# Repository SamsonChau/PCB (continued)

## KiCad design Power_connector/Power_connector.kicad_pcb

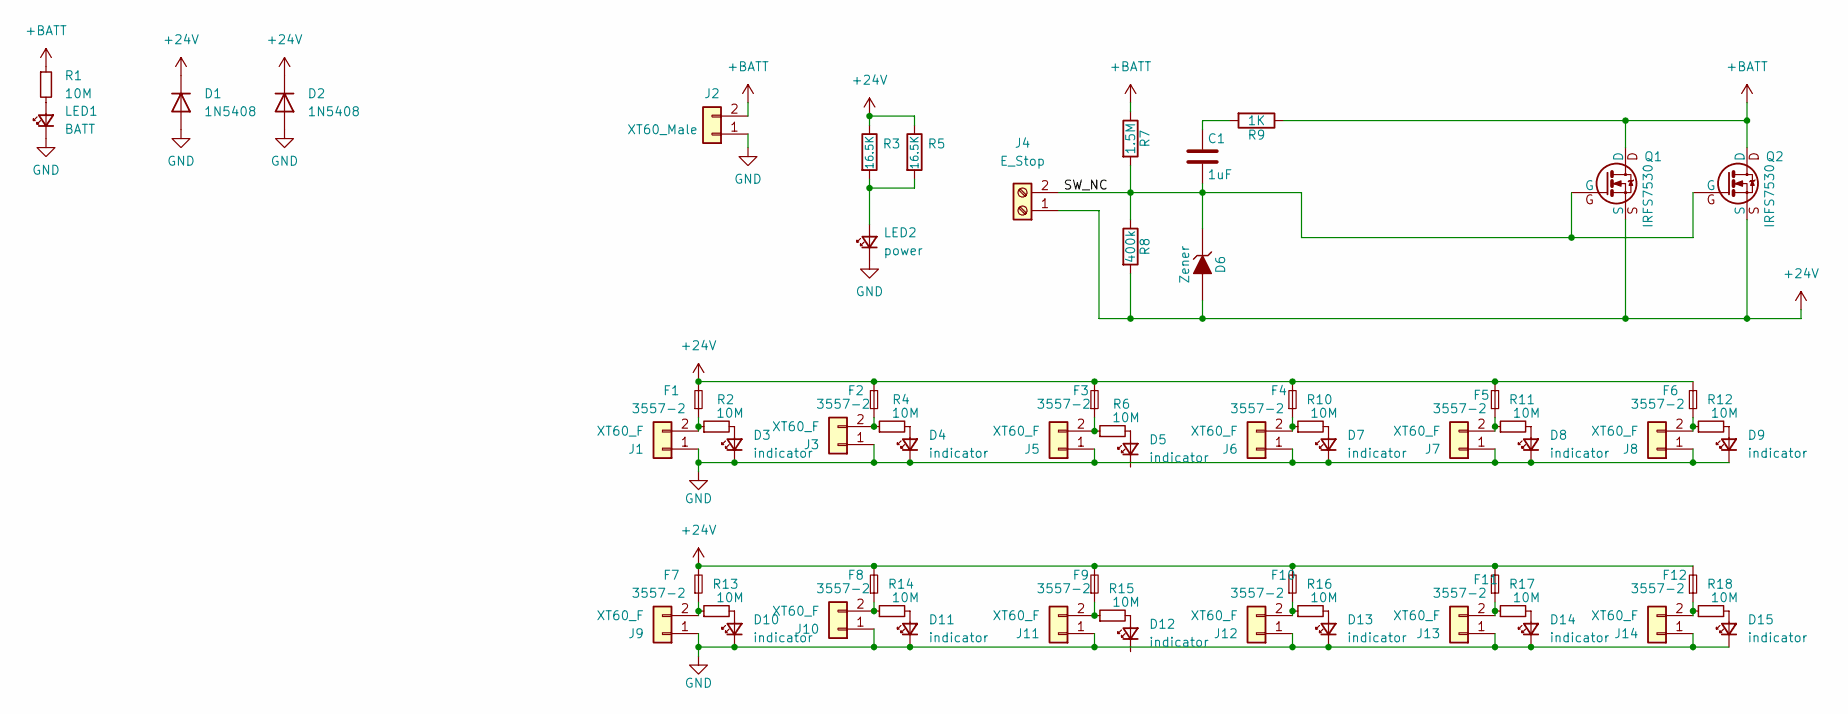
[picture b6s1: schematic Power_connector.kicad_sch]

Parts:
C1: 1uF; C_0805_2012Metric_Pad1.18x1.45mm_HandSolder
D1, D2: 1N5408; D_DO-201AD_P15.24mm_Horizontal
D3, D4, D5, D7, D8, D9, D10, D11, D12, D13, D14, D15: indicator; LED_0805_2012Metric
D6: Zener; D_SOD-123F
F1, F2, F3, F4, F5, F6, F7, F8, F9, F10, F11, F12: 3557-2; FUSE_3557-2
J1, J3, J5, J6, J7, J8, J9, J10, J11, J12, J13, J14: XT60_F; AMASS_XT60-F_1x02_P7.20mm_Vertical
J2: XT60_Male
J4: E_Stop; TerminalBlock_Phoenix_MKDS-1,5-2-5.08_1x02_P5.08mm_Horizont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
LED1: BATT; LED_0805_2012Metric_Pad1.15x1.40mm_HandSolder
LED2: power; LED_0805_2012Metric_Pad1.15x1.40mm_HandSolder
Q1, Q2: IRFS7530; D2PAK-7-GDS
R1, R2, R4, R6, R10, R11, R12, R13, R14, R15, R16, R17, R18: 10M; R_0805_2012Metric
R3, R5: 16.5K; R_1206_3216Metric_Pad1.30x1.75mm_HandSolder
R7: 1.5M; R_0805_2012Metric_Pad1.20x1.40mm_HandSolder
R8: 400k; R_0805_2012Metric_Pad1.20x1.40mm_HandSolder
R9: 1K; R_0805_2012Metric_Pad1.20x1.40mm_HandSolder

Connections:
+24V: D1.1 (K), D2.1 (K), D6.2 (A), F1.2, F2.2, F3.2, F4.2, F5.2, F6.2, F7.2, F8.2, F9.2, F10.2, F11.2, F12.2, J4.1, Q1.S, Q2.S, R3.1, R5.1, R8.2
+BATT: J2.2, Q1.D, Q2.D, R1.1, R7.1, R9.1
/SW_NC: C1.2, D6.1 (K), J4.2, Q1.G, Q2.G, R7.2, R8.1
GND: D1.2 (A), D2.2 (A), D3.1 (K), D4.1 (K), D7.1 (K), D8.1 (K), D9.1 (K), D10.1 (K), D11.1 (K), D13.1 (K), D14.1 (K), D15.1 (K), J1.1, J2.1, J3.1, J5.1, J6.1, J7.1, J8.1, J9.1, J10.1, J11.1, J12.1, J13.1, J14.1, LED1.1 (K), LED2.1 (K)
unnamed: C1.1, R9.2
unnamed: D3.2 (A), R2.2
unnamed: D4.2 (A), R4.2
unnamed: D5.2 (A), R6.2
unnamed: D7.2 (A), R10.2
unnamed: D8.2 (A), R11.2
unnamed: D9.2 (A), R12.2
unnamed: D10.2 (A), R13.2
unnamed: D11.2 (A), R14.2
unnamed: D12.2 (A), R15.2
unnamed: D13.2 (A), R16.2
unnamed: D14.2 (A), R17.2
unnamed: D15.2 (A), R18.2
unnamed: F1.1, J1.2, R2.1
unnamed: F2.1, J3.2, R4.1
unnamed: F3.1, J5.2, R6.1
unnamed: F4.1, J6.2, R10.1
unnamed: F5.1, J7.2, R11.1
unnamed: F6.1, J8.2, R12.1
unnamed: F7.1, J9.2, R13.1
unnamed: F8.1, J10.2, R14.1
unnamed: F9.1, J11.2, R15.1
unnamed: F10.1, J12.2, R16.1
unnamed: F11.1, J13.2, R17.1
unnamed: F12.1, J14.2, R18.1
unnamed: LED1.2 (A), R1.2
unnamed: LED2.2 (A), R3.2, R5.2

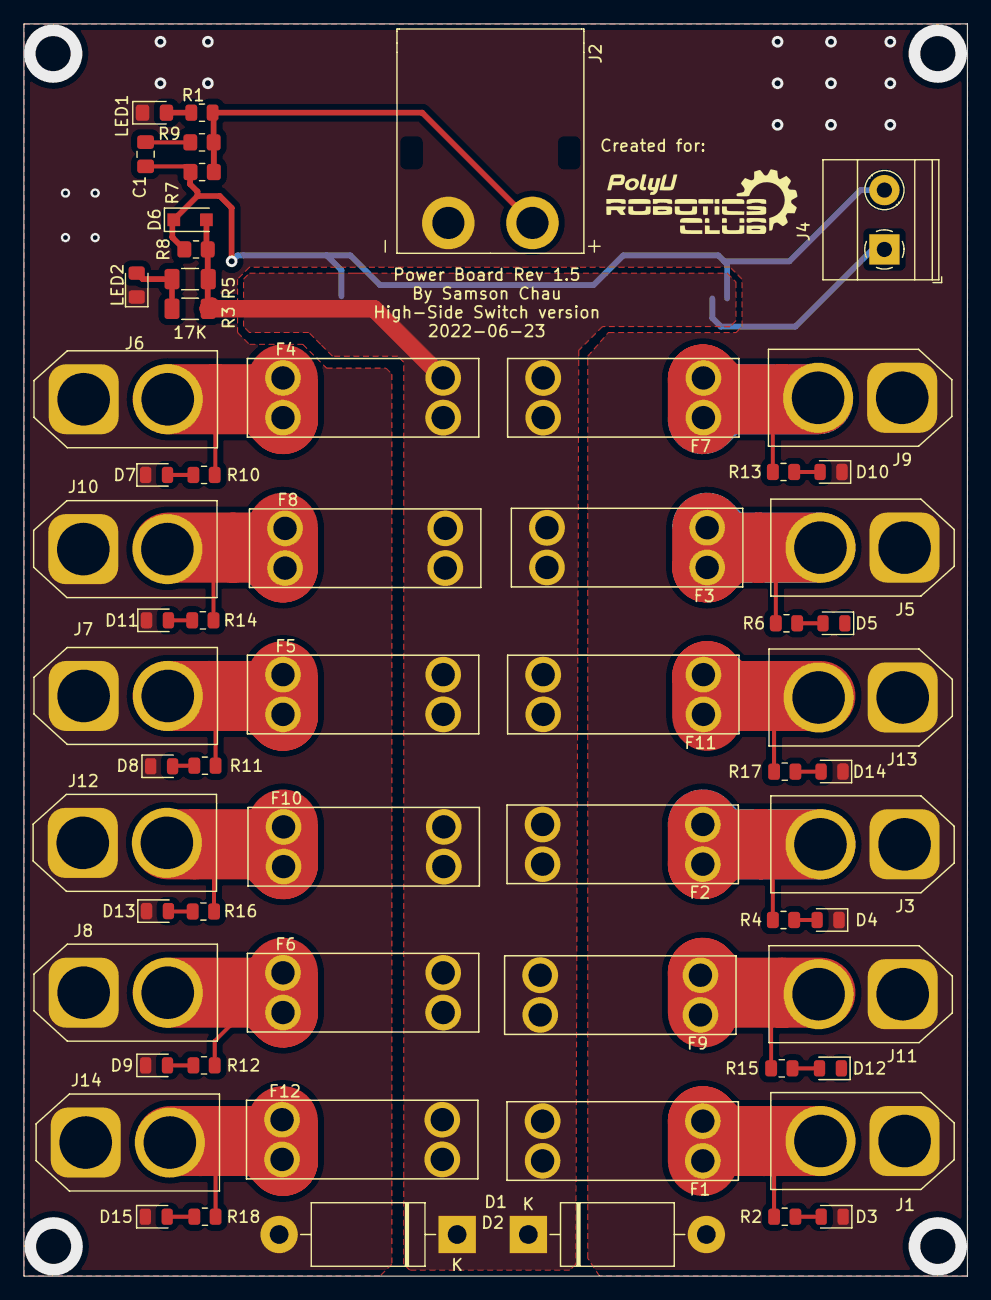
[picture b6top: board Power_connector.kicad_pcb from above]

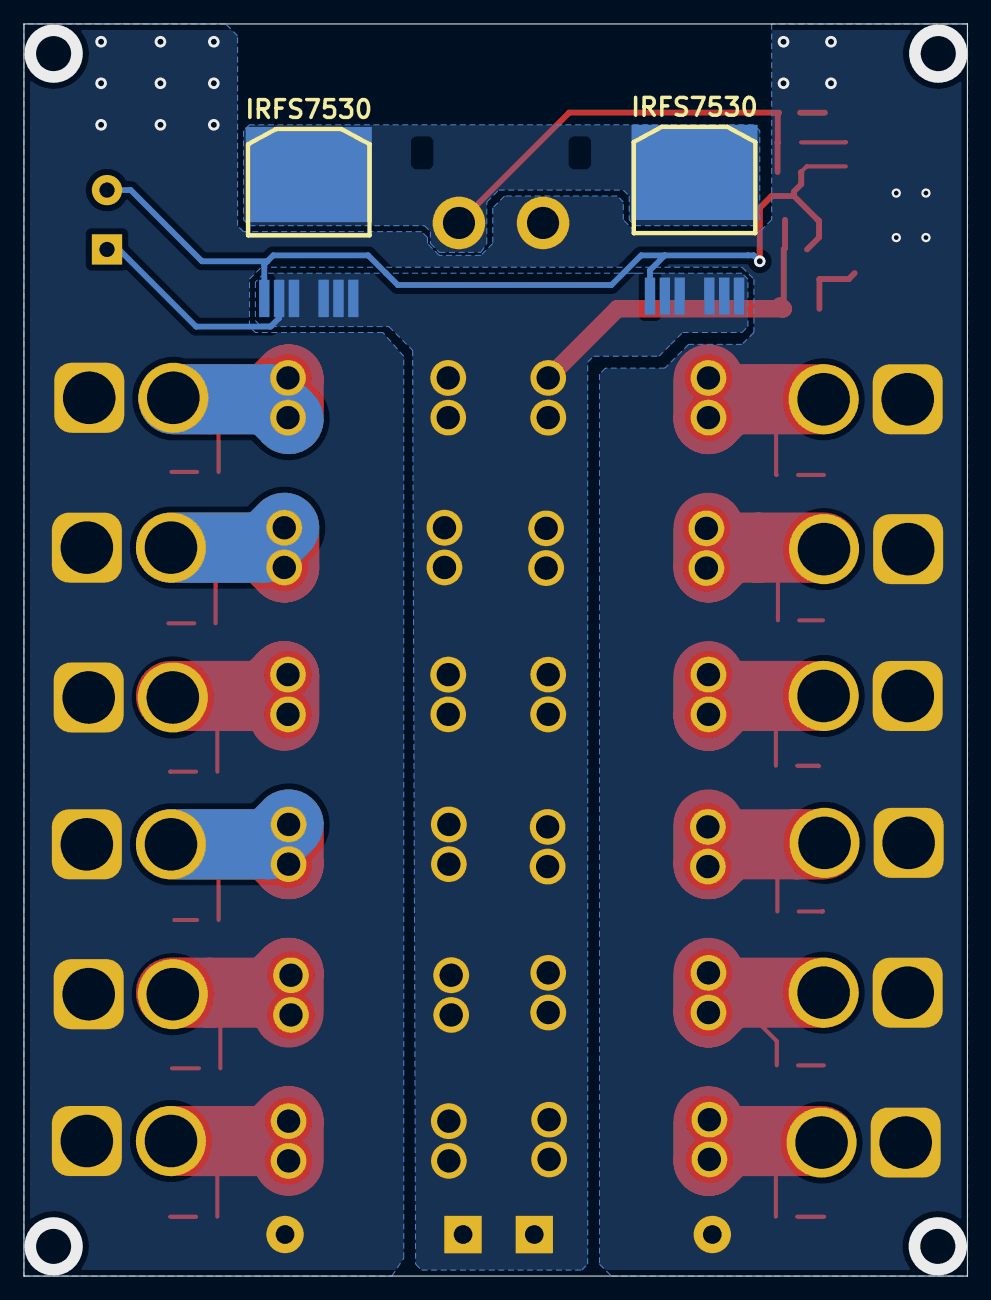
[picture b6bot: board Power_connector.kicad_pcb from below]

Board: 2 copper layers, 80.8 x 107.2 mm, 64 parts (2 on the bottom side), 31 nets.

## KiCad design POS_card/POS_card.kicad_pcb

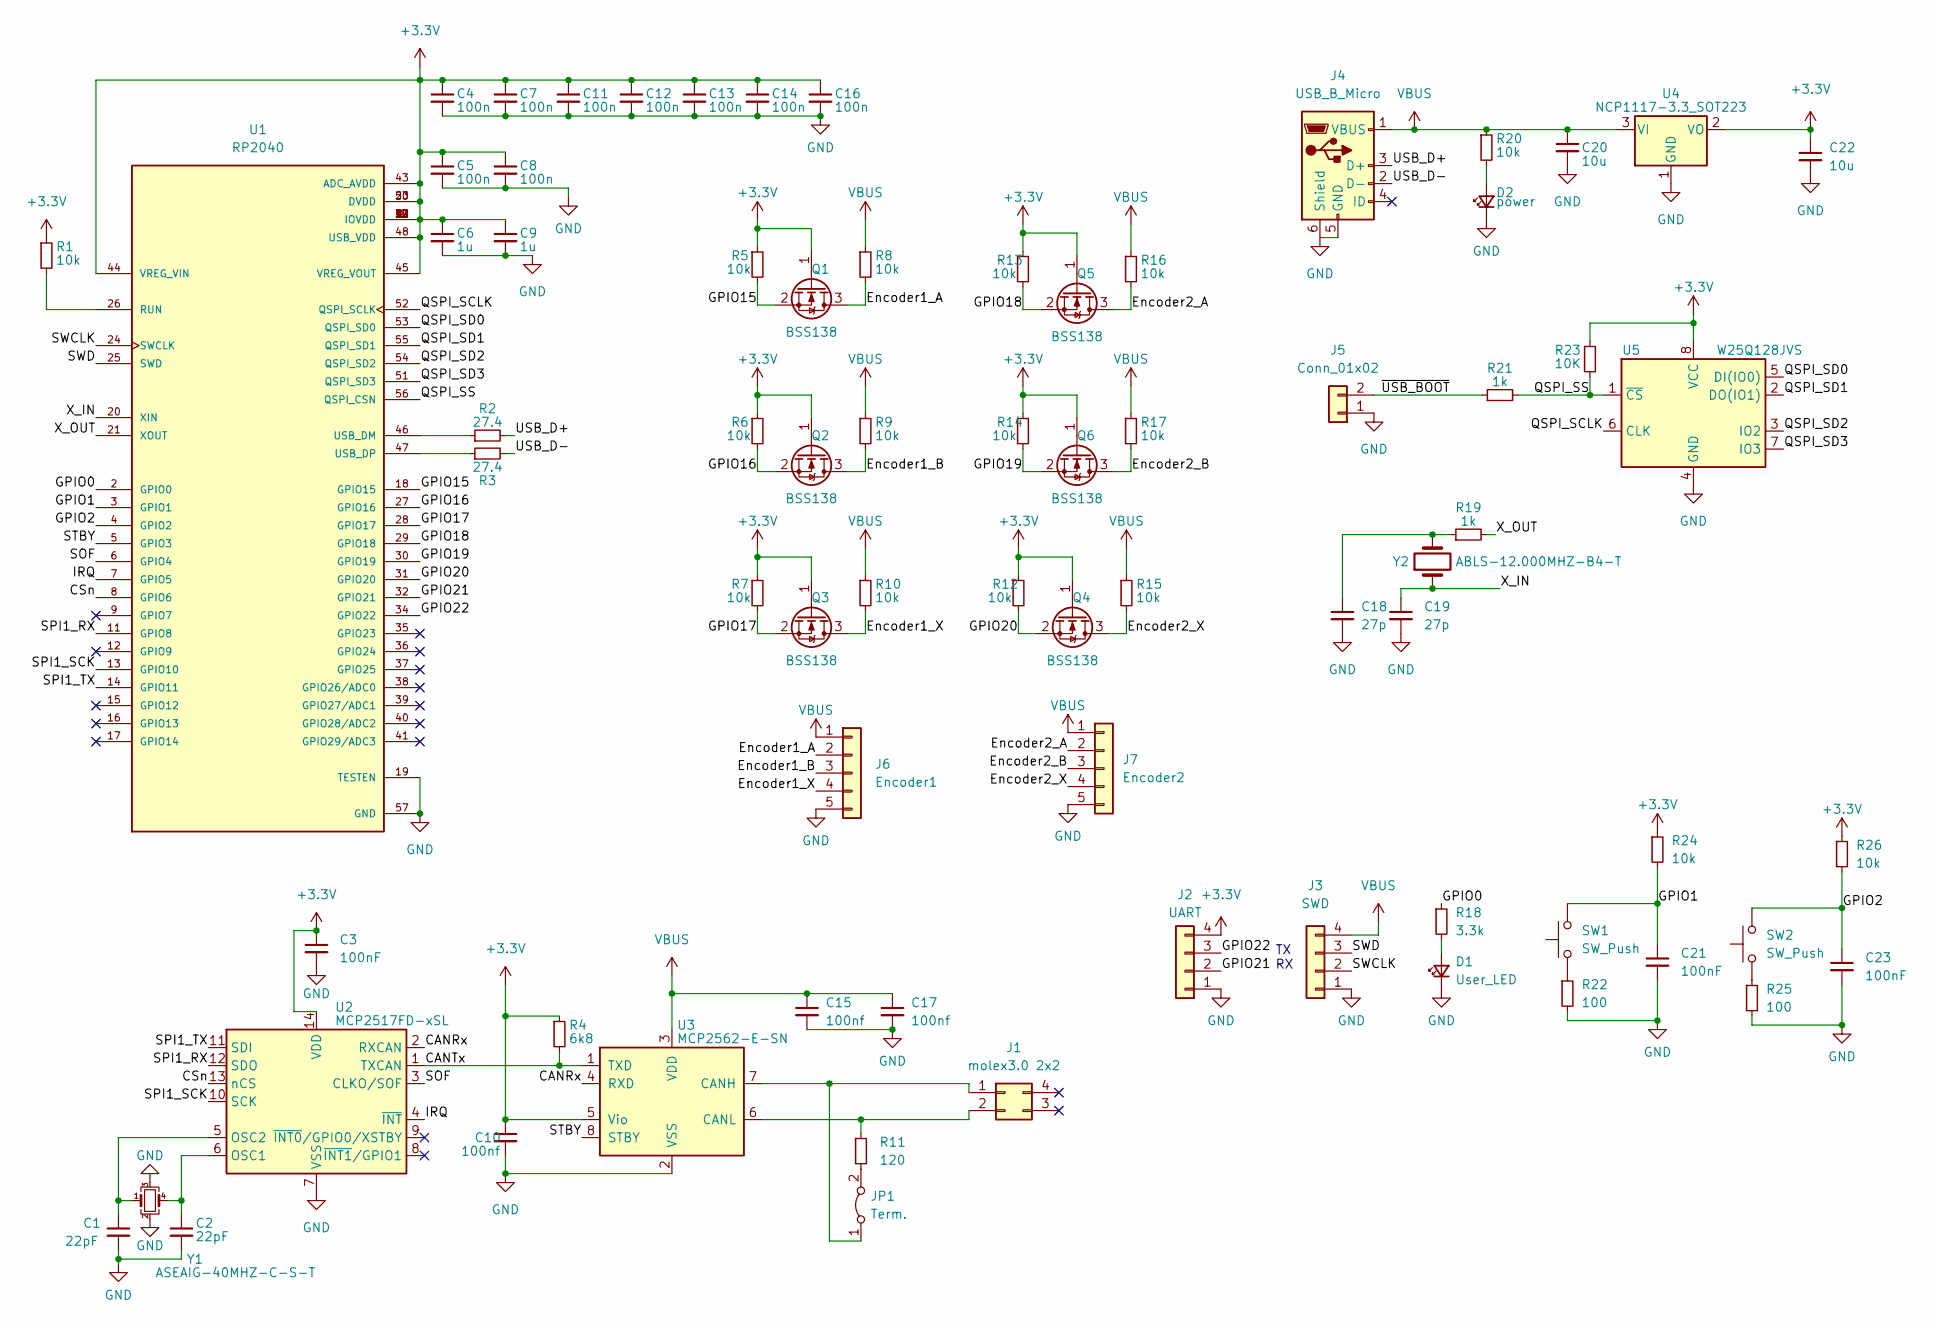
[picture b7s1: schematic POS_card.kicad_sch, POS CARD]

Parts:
C1, C2: 22pF; C_0402_1005Metric
C3, C21: 100nF; C_0402_1005Metric
C4, C5, C7, C8, C11, C12, C13, C14, C16: 100n; C_0402_1005Metric
C6, C9: 1u; C_0402_1005Metric
C10, C15, C17: 100nf; C_0402_1005Metric
C18, C19: 27p; C_0402_1005Metric
C20, C22: 10u; C_0603_1608Metric
C23: 100nF; C_0402_1005Metric_Pad0.74x0.62mm_HandSolder
D1: User_LED; LED_0402_1005Metric
D2: power; LED_0402_1005Metric
J1: molex3.0 2x2; Molex_Micro-Fit_3.0_43045-0412_2x02_P3.00mm_Vertical
J2: UART; PinHeader_1x04_P2.54mm_Vertical
J3: SWD; PinHeader_1x04_P2.54mm_Vertical
J4: USB_B_Micro; USB_Micro-B_Molex-105017-0001
J5: Conn_01x02; PinHeader_1x02_P2.54mm_Vertical
J6: Encoder1; JST_PH_B5B-PH-K_1x05_P2.00mm_Vertical
J7: Encoder2; JST_PH_B5B-PH-K_1x05_P2.00mm_Vertical
JP1: Term.; TestPoint_Bridge_Pitch2.0mm_Drill0.7mm
Q1, Q2, Q3, Q4, Q5, Q6: BSS138; SOT-23
R1, R5, R6, R7, R8, R9, R10, R12, R13, R14, R15, R16, R17, R20, R24, R26: 10k; R_0402_1005Metric
R2, R3: 27.4; R_0402_1005Metric
R4: 6k8; R_0402_1005Metric
R11: 120; R_0402_1005Metric
R18: 3.3k; R_0402_1005Metric
R19, R21: 1k; R_0402_1005Metric
R22, R25: 100; R_0402_1005Metric
R23: 10K; R_0402_1005Metric
SW1, SW2: SW_Push; SW_Push_1P1T_NO_6x6mm_H9.5mm
U1: RP2040; QFN40P700X700X90-57N; PARTREV 1.6.1
U2: MCP2517FD-xSL; SOIC-14_3.9x8.7mm_P1.27mm
U3: MCP2562-E-SN; SOIC-8_3.9x4.9mm_P1.27mm
U4: NCP1117-3.3_SOT223; SOT-223-3_TabPin2
U5: W25Q128JVS; SOIC-8_5.23x5.23mm_P1.27mm
Y1: ASEAIG-40MHZ-C-S-T; Crystal_SMD_TXC_7M-4Pin_3.2x2.5mm
Y2: ABLS-12.000MHZ-B4-T; Crystal_SMD_HC49-SD

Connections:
+3V3: C3.1, C4.1, C5.1, C6.1, C7.1, C8.1, C9.1, C10.1, C11.1, C12.1, C13.1, C14.1, C16.1, C22.1, J2.4, Q1.1 (G), Q2.1 (G), Q3.1 (G), Q4.1 (G), Q5.1 (G), Q6.1 (G), R1.1, R4.1, R5.1, R6.1, R7.1, R12.1, R13.1, R14.1, R23.1, R24.1, R26.1, U1.1 (IOVDD), U1.10 (IOVDD), U1.22 (IOVDD), U1.23 (DVDD), U1.33 (IOVDD), U1.42 (IOVDD), U1.43 (ADC_AVDD), U1.44 (VREG_VIN), U1.45 (VREG_VOUT), U1.48 (USB_VDD), U1.49 (IOVDD), U1.50 (DVDD), U2.14 (VDD), U3.5 (Vio), U4.2 (VO), U5.8 (VCC)
/CANRx: U2.2 (RXCAN), U3.4 (RXD)
/CANTx: R4.2, U2.1 (TXCAN), U3.1 (TXD)
/CSn: U1.8 (GPIO6), U2.13 (nCS)
/Encoder1_A: J6.2, Q1.3 (D), R8.2
/Encoder1_B: J6.3, Q2.3 (D), R9.2
/Encoder1_X: J6.4, Q3.3 (D), R10.2
/Encoder2_A: J7.2, Q5.3 (D), R16.2
/Encoder2_B: J7.3, Q6.3 (D), R17.2
/Encoder2_X: J7.4, Q4.3 (D), R15.2
/GPIO0: R18.1, U1.2 (GPIO0)
/GPIO1: C21.1, R24.2, SW1.2, U1.3 (GPIO1)
/GPIO2: C23.1, R26.2, SW2.2, U1.4 (GPIO2)
/GPIO15: Q1.2 (S), R5.2, U1.18 (GPIO15)
/GPIO16: Q2.2 (S), R6.2, U1.27 (GPIO16)
/GPIO17: Q3.2 (S), R7.2, U1.28 (GPIO17)
/GPIO18: Q5.2 (S), R13.2, U1.29 (GPIO18)
/GPIO19: Q6.2 (S), R14.2, U1.30 (GPIO19)
/GPIO20: Q4.2 (S), R12.2, U1.31 (GPIO20)
/GPIO21: J2.2, U1.32 (GPIO21)
/GPIO22: J2.3, U1.34 (GPIO22)
/IRQ: U1.7 (GPIO5), U2.4 (~INT)
/QSPI_SCLK: U1.52 (QSPI_SCLK), U5.6 (CLK)
/QSPI_SD0: U1.53 (QSPI_SD0), U5.5 (DI(IO0))
/QSPI_SD1: U1.55 (QSPI_SD1), U5.2 (DO(IO1))
/QSPI_SD2: U1.54 (QSPI_SD2), U5.3 (IO2)
/QSPI_SD3: U1.51 (QSPI_SD3), U5.7 (IO3)
/QSPI_SS: R21.2, R23.2, U1.56 (QSPI_CSN), U5.1 (~CS)
/SOF: U1.6 (GPIO4), U2.3 (CLKO/SOF)
/SPI1_RX: U1.11 (GPIO8), U2.12 (SDO)
/SPI1_SCK: U1.13 (GPIO10), U2.10 (SCK)
/SPI1_TX: U1.14 (GPIO11), U2.11 (SDI)
/STBY: U1.5 (GPIO3), U3.8 (STBY)
/SWCLK: J3.2, U1.24 (SWCLK)
/SWD: J3.3, U1.25 (SWD)
/USB_D+: J4.3 (D+), R2.2
/USB_D-: J4.2 (D-), R3.2
/X_IN: C19.1, U1.20 (XIN), Y2.1
/X_OUT: R19.2, U1.21 (XOUT)
/~USB_BOOT: J5.2, R21.1
GND: C1.2, C2.2, C3.2, C4.2, C5.2, C6.2, C7.2, C8.2, C9.2, C10.2, C11.2, C12.2, C13.2, C14.2, C15.2, C16.2, C17.2, C18.2, C19.2, C20.2, C21.2, C22.2, C23.2, D1.1 (K), D2.1 (K), J2.1, J3.1, J4.5 (GND), J4.6 (Shield), J5.1, J6.5, J7.5, R22.2, R25.2, U1.19 (TESTEN), U1.57 (GND), U2.7 (VSS), U3.2 (VSS), U4.1 (GND), U5.4 (GND), Y1.2, Y1.3
unnamed: C1.1, U2.5 (OSC2), Y1.1
unnamed: C2.1, U2.6 (OSC1), Y1.4
unnamed: C18.1, R19.1, Y2.2
unnamed: D1.2 (A), R18.2
unnamed: D2.2 (A), R20.2
unnamed: J1.1, JP1.1 (A), U3.7 (CANH)
unnamed: J1.2, R11.1, U3.6 (CANL)
unnamed: JP1.2 (B), R11.2
unnamed: R1.2, U1.26 (RUN)
unnamed: R2.1, U1.46 (USB_DM)
unnamed: R3.1, U1.47 (USB_DP)
unnamed: R22.1, SW1.1
unnamed: R25.1, SW2.1
VBUS: C15.1, C17.1, C20.1, J3.4, J4.1 (VBUS), J6.1, J7.1, R8.1, R9.1, R10.1, R15.1, R16.1, R17.1, R20.1, U3.3 (VDD), U4.3 (VI)

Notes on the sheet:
TX RX

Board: 2 copper layers, 74 parts (0 on the bottom side), 54 nets, no tracks yet.

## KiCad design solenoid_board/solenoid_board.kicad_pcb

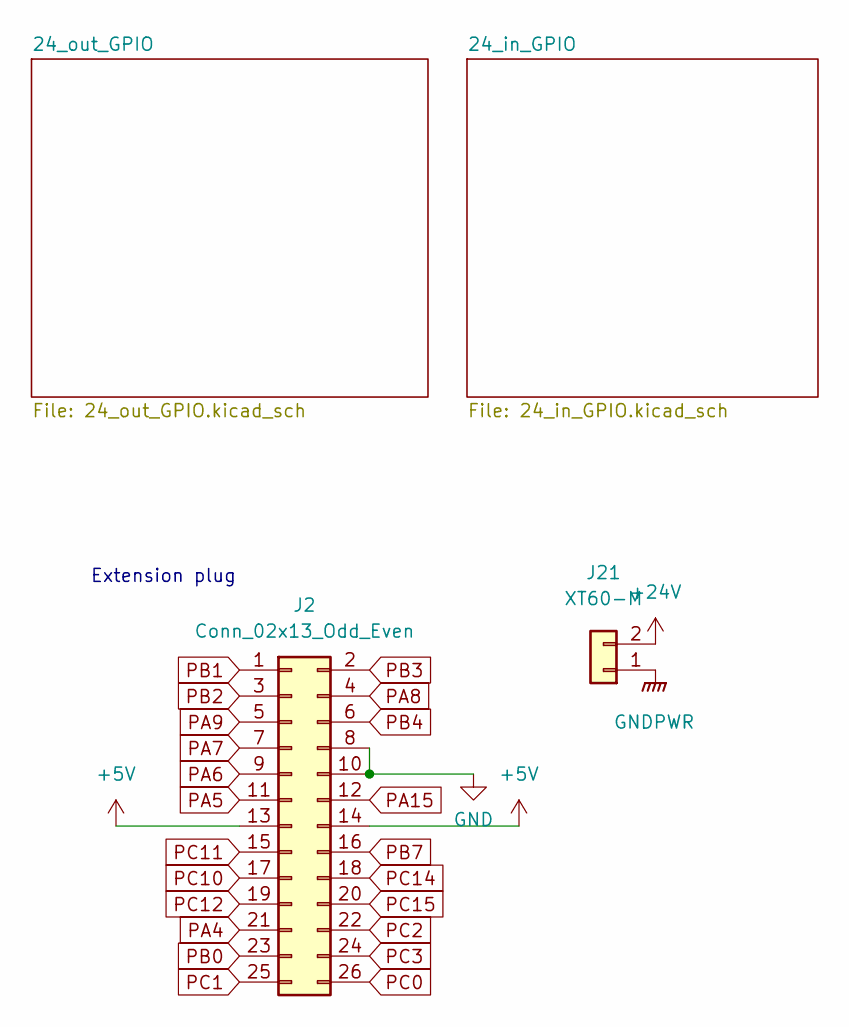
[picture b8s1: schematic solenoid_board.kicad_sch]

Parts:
J2: Conn_02x13_Odd_Even; IDC-Header_2x13_P2.54mm_Vertical
J21: XT60-M

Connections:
+5V: J2.13, J2.14; also elsewhere on the board
+24V: J21.2; also elsewhere on the board
PA4: J2.21; also elsewhere on the board
PA5: J2.11; also elsewhere on the board
PA6: J2.9; also elsewhere on the board
PA7: J2.7; also elsewhere on the board
PA8: J2.4
PA9: J2.5; also elsewhere on the board
PA15: J2.12
PB0: J2.23; also elsewhere on the board
PB1: J2.1; also elsewhere on the board
PB2: J2.3; also elsewhere on the board
PB3: J2.2
PB4: J2.6
PB7: J2.16; also elsewhere on the board
PC0: J2.26; also elsewhere on the board
PC1: J2.25; also elsewhere on the board
PC2: J2.22; also elsewhere on the board
PC3: J2.24; also elsewhere on the board
PC10: J2.17; also elsewhere on the board
PC11: J2.15; also elsewhere on the board
PC12: J2.19; also elsewhere on the board
PC14: J2.18; also elsewhere on the board
PC15: J2.20; also elsewhere on the board

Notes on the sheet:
Extension plug

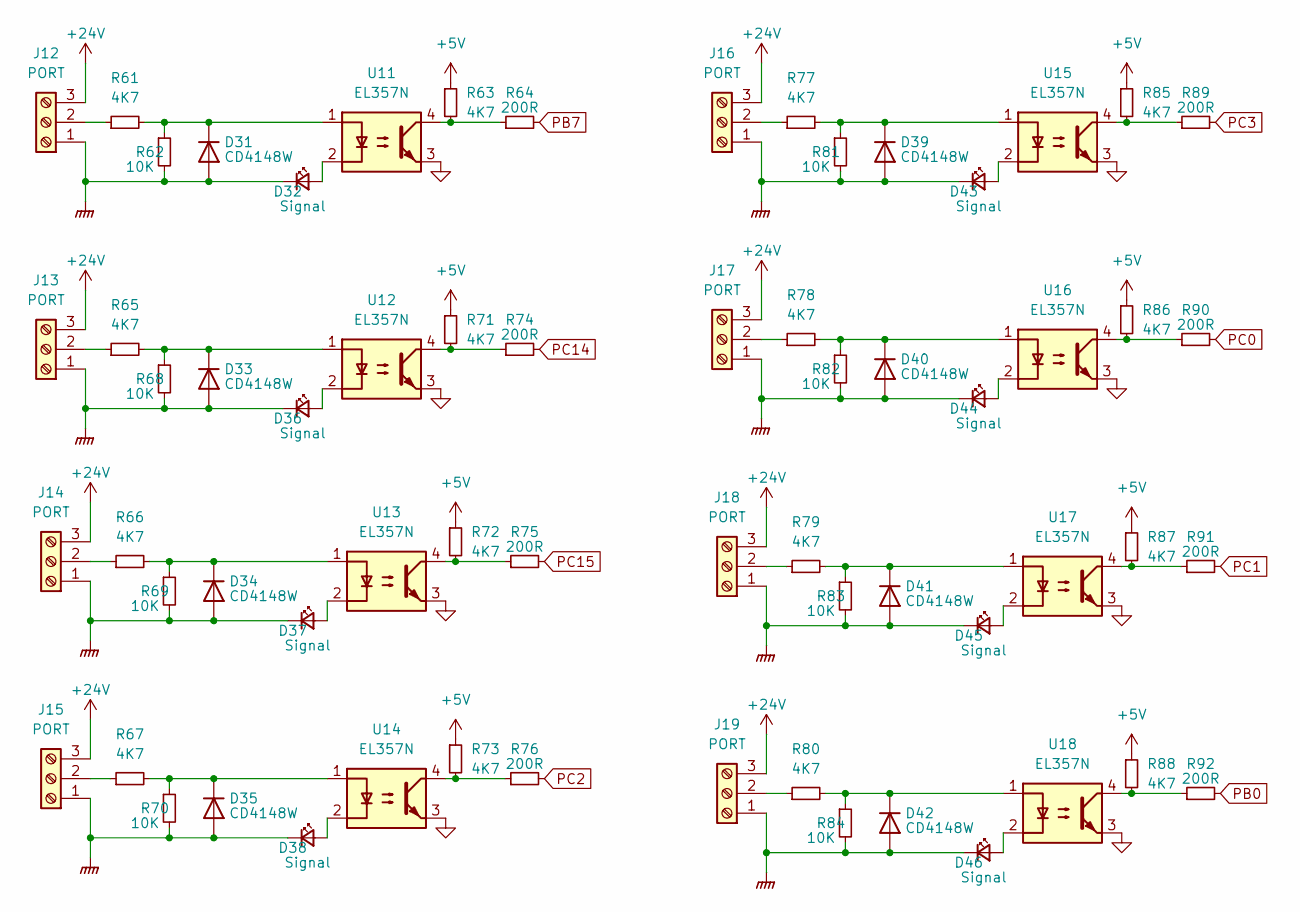
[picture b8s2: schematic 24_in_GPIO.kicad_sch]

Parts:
D31, D33, D34, D35, D39, D40, D41, D42: CD4148W; D_1206_3216Metric
D32, D36, D37, D38, D43, D44, D45, D46: Signal; LED_0805_2012Metric_Pad1.15x1.40mm_HandSolder
J12, J13, J14, J15, J16, J17, J18, J19: PORT; TerminalBlock_Phoenix_PT-1,5-3-3.5-H_1x03_P3.50mm_Horizontal
R61, R63, R65, R66, R67, R71, R72, R73, R77, R78, R79, R80, R85, R86, R87, R88: 4K7; R_0805_2012Metric_Pad1.20x1.40mm_HandSolder
R62, R68, R69, R70, R81, R82, R83, R84: 10K; R_0805_2012Metric_Pad1.20x1.40mm_HandSolder
R64, R74, R75, R76, R89, R90, R91, R92: 200R; R_0805_2012Metric_Pad1.20x1.40mm_HandSolder
U11, U12, U13, U14, U15, U16, U17, U18: EL357N

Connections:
+5V: R63.1, R71.1, R72.1, R73.1, R85.1, R86.1, R87.1, R88.1; also elsewhere on the board
+24V: J12.3, J13.3, J14.3, J15.3, J16.3, J17.3, J18.3, J19.3; also elsewhere on the board
unnamed: D31.1 (K), R61.2, R62.1, U11.1
unnamed: D32.2 (A), U11.2
unnamed: D33.1 (K), R65.2, R68.1, U12.1
unnamed: D34.1 (K), R66.2, R69.1, U13.1
unnamed: D35.1 (K), R67.2, R70.1, U14.1
unnamed: D36.2 (A), U12.2
unnamed: D37.2 (A), U13.2
unnamed: D38.2 (A), U14.2
unnamed: D39.1 (K), R77.2, R81.1, U15.1
unnamed: D40.1 (K), R78.2, R82.1, U16.1
unnamed: D41.1 (K), R79.2, R83.1, U17.1
unnamed: D42.1 (K), R80.2, R84.1, U18.1
unnamed: D43.2 (A), U15.2
unnamed: D44.2 (A), U16.2
unnamed: D45.2 (A), U17.2
unnamed: D46.2 (A), U18.2
unnamed: J12.2, R61.1
unnamed: J13.2, R65.1
unnamed: J14.2, R66.1
unnamed: J15.2, R67.1
unnamed: J16.2, R77.1
unnamed: J17.2, R78.1
unnamed: J18.2, R79.1
unnamed: J19.2, R80.1
unnamed: R63.2, R64.1, U11.4
unnamed: R71.2, R74.1, U12.4
unnamed: R72.2, R75.1, U13.4
unnamed: R73.2, R76.1, U14.4
unnamed: R85.2, R89.1, U15.4
unnamed: R86.2, R90.1, U16.4
unnamed: R87.2, R91.1, U17.4
unnamed: R88.2, R92.1, U18.4
PB0: R92.2; also elsewhere on the board
PB7: R64.2; also elsewhere on the board
PC0: R90.2; also elsewhere on the board
PC1: R91.2; also elsewhere on the board
PC2: R76.2; also elsewhere on the board
PC3: R89.2; also elsewhere on the board
PC14: R74.2; also elsewhere on the board
PC15: R75.2; also elsewhere on the board

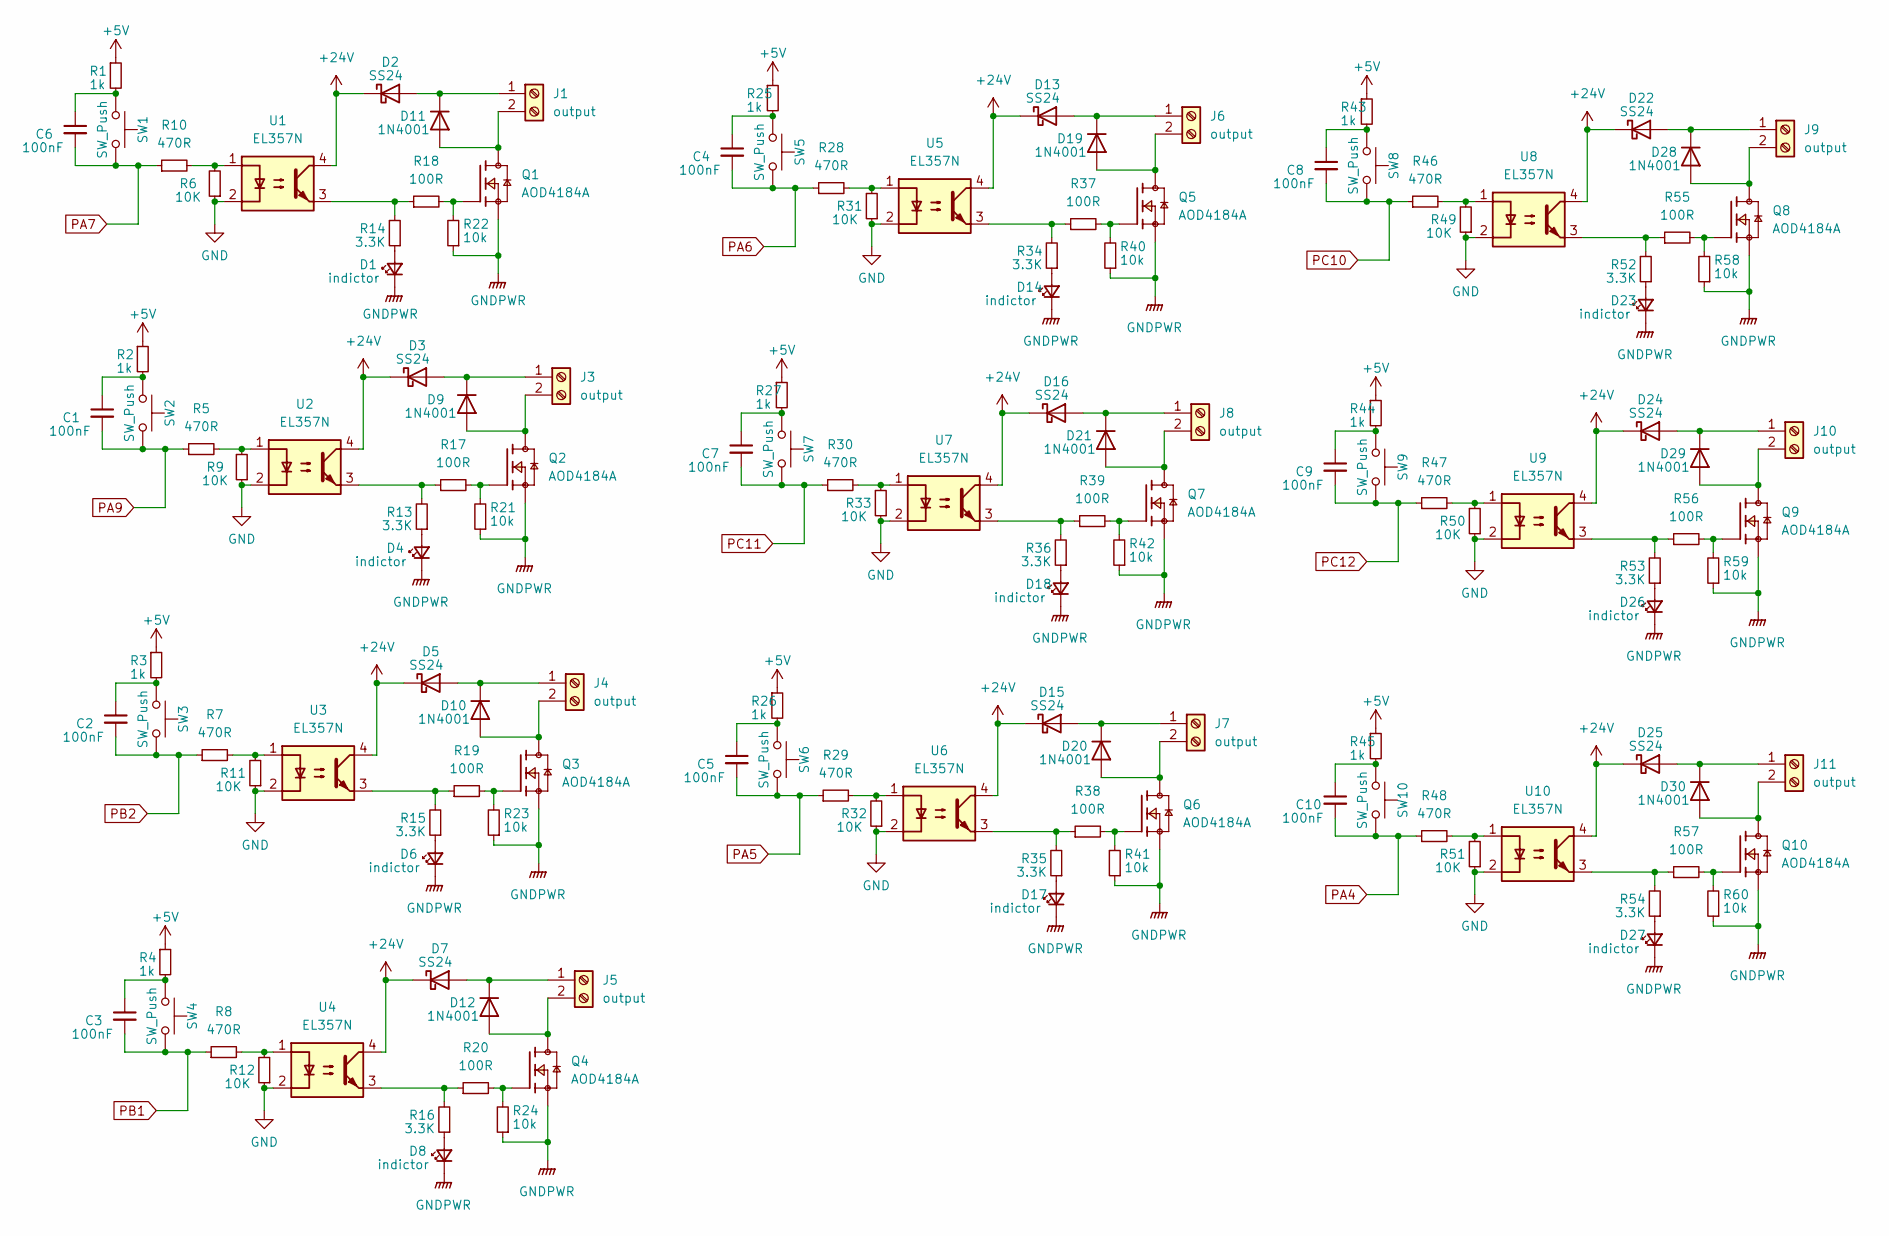
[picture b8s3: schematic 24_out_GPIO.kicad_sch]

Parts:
C1, C2, C3, C4, C5, C6, C7, C8, C9, C10: 100nF; C_0805_2012Metric_Pad1.18x1.45mm_HandSolder
D1, D4, D6, D8, D14, D17, D18, D23, D26, D27: indictor; LED_0805_2012Metric_Pad1.15x1.40mm_HandSolder
D2, D3, D5, D7, D13, D15, D16, D22, D24, D25: SS24; D_SMB
D9, D10, D11, D12, D19, D20, D21, D28, D29, D30: 1N4001; D_DO-41_SOD81_P10.16mm_Horizontal
J1, J3, J4, J5, J6, J7, J8, J9, J10, J11: output; TerminalBlock_Phoenix_PT-1,5-2-5.0-H_1x02_P5.00mm_Horizontal
Q1, Q2, Q3, Q4, Q5, Q6, Q7, Q8, Q9, Q10: AOD4184A; DPAK228P994X240-4N; PARTREV 0
R1, R2, R3, R4, R25, R26, R27, R43, R44, R45: 1k; R_0805_2012Metric_Pad1.20x1.40mm_HandSolder
R5, R7, R8, R10, R28, R29, R30, R46, R47, R48: 470R; R_0805_2012Metric_Pad1.20x1.40mm_HandSolder
R6, R9, R11, R12, R31, R32, R33, R49, R50, R51: 10K; R_0805_2012Metric_Pad1.20x1.40mm_HandSolder
R13, R14, R15, R16, R34, R35, R36, R52, R53, R54: 3.3K; R_0805_2012Metric_Pad1.20x1.40mm_HandSolder
R17, R18, R19, R20, R37, R38, R39, R55, R56, R57: 100R; R_0805_2012Metric_Pad1.20x1.40mm_HandSolder
R21, R22, R23, R24, R40, R41, R42, R58, R59, R60: 10k; R_0805_2012Metric_Pad1.20x1.40mm_HandSolder
SW1, SW2, SW3, SW4, SW5, SW6, SW7, SW8, SW9, SW10: SW_Push; SW_SPST_TL3305A
U1, U2, U3, U4, U5, U6, U7, U8, U9, U10: EL357N

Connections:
+5V: R1.1, R2.1, R3.1, R4.1, R25.1, R26.1, R27.1, R43.1, R44.1, R45.1; also elsewhere on the board
+24V: D2.1 (K), D3.1 (K), D5.1 (K), D7.1 (K), D13.1 (K), D15.1 (K), D16.1 (K), D22.1 (K), D24.1 (K), D25.1 (K), U1.4, U2.4, U3.4, U4.4, U5.4, U6.4, U7.4, U8.4, U9.4, U10.4; also elsewhere on the board
unnamed: C1.1, R2.2, SW2.1
unnamed: C2.1, R3.2, SW3.1
unnamed: C3.1, R4.2, SW4.1
unnamed: C4.1, R25.2, SW5.1
unnamed: C5.1, R26.2, SW6.1
unnamed: C6.1, R1.2, SW1.1
unnamed: C7.1, R27.2, SW7.1
unnamed: C8.1, R43.2, SW8.1
unnamed: C9.1, R44.2, SW9.1
unnamed: C10.1, R45.2, SW10.1
unnamed: D1.2 (A), R14.1
unnamed: D3.2 (A), D9.1 (K), J3.1
unnamed: D4.2 (A), R13.1
unnamed: D6.2 (A), R15.1
unnamed: D8.2 (A), R16.1
unnamed: D9.2 (A), J3.2, Q2.4
unnamed: D5.2 (A), D10.1 (K), J4.1
unnamed: D10.2 (A), J4.2, Q3.4
unnamed: D2.2 (A), D11.1 (K), J1.1
unnamed: D11.2 (A), J1.2, Q1.4
unnamed: D7.2 (A), D12.1 (K), J5.1
unnamed: D12.2 (A), J5.2, Q4.4
unnamed: D13.2 (A), D19.1 (K), J6.1
unnamed: D14.2 (A), R34.1
unnamed: D15.2 (A), D20.1 (K), J7.1
unnamed: D16.2 (A), D21.1 (K), J8.1
unnamed: D17.2 (A), R35.1
unnamed: D18.2 (A), R36.1
unnamed: D19.2 (A), J6.2, Q5.4
unnamed: D20.2 (A), J7.2, Q6.4
unnamed: D21.2 (A), J8.2, Q7.4
unnamed: D22.2 (A), D28.1 (K), J9.1
unnamed: D23.2 (A), R52.1
unnamed: D24.2 (A), D29.1 (K), J10.1
unnamed: D25.2 (A), D30.1 (K), J11.1
unnamed: D26.2 (A), R53.1
unnamed: D27.2 (A), R54.1
unnamed: D28.2 (A), J9.2, Q8.4
unnamed: D29.2 (A), J10.2, Q9.4
unnamed: D30.2 (A), J11.2, Q10.4
unnamed: Q1.1, R18.2, R22.2
unnamed: Q2.1, R17.2, R21.2
unnamed: Q3.1, R19.2, R23.2
unnamed: Q4.1, R20.2, R24.2
unnamed: Q5.1, R37.2, R40.2
unnamed: Q6.1, R38.2, R41.2
unnamed: Q7.1, R39.2, R42.2
unnamed: Q8.1, R55.2, R58.2
unnamed: Q9.1, R56.2, R59.2
unnamed: Q10.1, R57.2, R60.2
unnamed: R5.2, R9.2, U2.1
unnamed: R6.2, R10.2, U1.1
unnamed: R7.2, R11.2, U3.1
unnamed: R8.2, R12.2, U4.1
unnamed: R13.2, R17.1, U2.3
unnamed: R14.2, R18.1, U1.3
unnamed: R15.2, R19.1, U3.3
unnamed: R16.2, R20.1, U4.3
unnamed: R28.2, R31.2, U5.1
unnamed: R29.2, R32.2, U6.1
unnamed: R30.2, R33.2, U7.1
unnamed: R34.2, R37.1, U5.3
unnamed: R35.2, R38.1, U6.3
unnamed: R36.2, R39.1, U7.3
unnamed: R46.2, R49.2, U8.1
unnamed: R47.2, R50.2, U9.1
unnamed: R48.2, R51.2, U10.1
unnamed: R52.2, R55.1, U8.3
unnamed: R53.2, R56.1, U9.3
unnamed: R54.2, R57.1, U10.3
PA4: C10.2, R48.1, SW10.2; also elsewhere on the board
PA5: C5.2, R29.1, SW6.2; also elsewhere on the board
PA6: C4.2, R28.1, SW5.2; also elsewhere on the board
PA7: C6.2, R10.1, SW1.2; also elsewhere on the board
PA9: C1.2, R5.1, SW2.2; also elsewhere on the board
PB1: C3.2, R8.1, SW4.2; also elsewhere on the board
PB2: C2.2, R7.1, SW3.2; also elsewhere on the board
PC10: C8.2, R46.1, SW8.2; also elsewhere on the board
PC11: C7.2, R30.1, SW7.2; also elsewhere on the board
PC12: C9.2, R47.1, SW9.2; also elsewhere on the board

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
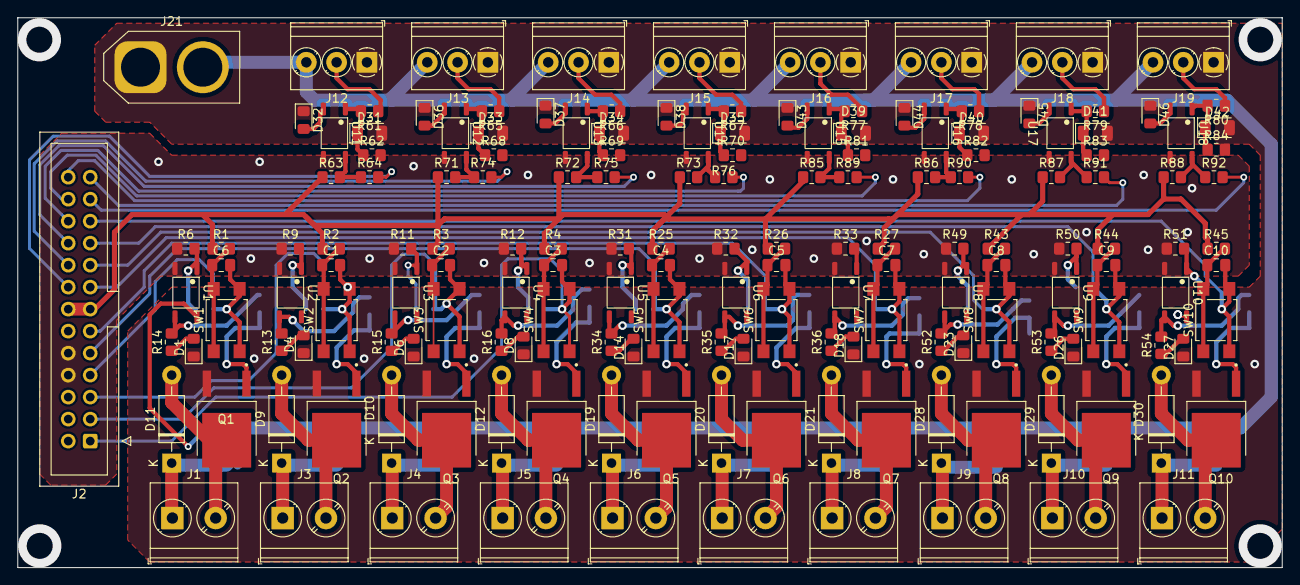
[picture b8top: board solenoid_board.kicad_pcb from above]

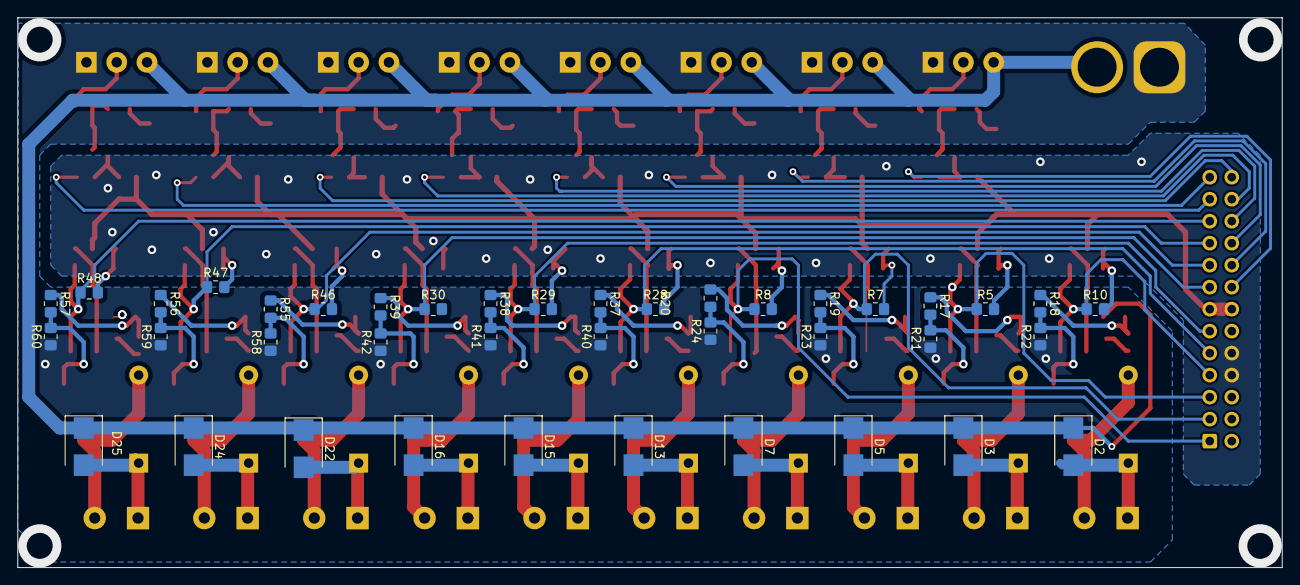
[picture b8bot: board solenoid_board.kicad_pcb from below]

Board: 2 copper layers, 146.1 x 63.5 mm, 206 parts (40 on the bottom side), 124 nets.

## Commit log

2022-01-27 extracted project folder
2022-01-27 added gerber
2022-01-27 add all
2022-01-27 add lib
2022-01-31 shield
2022-01-31 add bullyU
2022-01-31 change
2022-02-07 Raymond
2022-02-08 mod plug
2022-02-08 mod graphic
2022-02-08 new_board
2022-02-08 graphics
2022-02-08 diode
2022-02-09 add diode
2022-02-09 power_board
2022-02-10 power board
2022-02-10 boards
2022-02-15 terminal
2022-02-16 added photos
2022-02-21 gerber
2022-02-22 fix design in arduinoshield
2022-02-22 POS_CARD
2022-02-28 POS_update
2022-03-07 new project
2022-03-22 24v solenoid update
2022-04-04 Newclueo_Board
2022-04-06 add V2 board
2022-04-07 added NucleoF446
2022-04-08 added power board
2022-04-12 solenoid board
2022-04-13 test
2022-04-14 added cad
2022-04-19 power connector added
2022-04-25 added board
2022-05-13 change footprint
2022-05-20 powerboard mod
2022-05-23 ESP,Power board update
2022-05-24 esp32 fixed canbus
2022-05-25 ESP Board Update
2022-05-26 new shield
2022-05-27 arduino_shield update
2022-06-01 regular update
2022-06-23 new esp
2022-06-27 added new project
2022-08-18 new arduio shield
2022-08-22 v2.1 added BOM
2022-08-23 vesc shield update
2022-08-24 fixed bug
